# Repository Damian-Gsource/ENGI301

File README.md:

# ENGI301: Drone project
Repository for ENGI301 course work
The first project that was worked on for this course was a DIY drone/quadcopter fitted with a camera.
This drone would be able to fly remotely and have a camera attached to it as well. It is worth noting that the drone is a continuous work in progress. 

Needed Installations

(Pocketbeagle)

sudo apt-get update

sudo apt-get install build-essential python-dev python-setuptools python-smbus -y

sudo apt-get install python-pip python3-pip -y

sudo apt-get install zip

sudo pip3 install --upgrade setuptools

sudo pip3 install --upgrade Adafruit_BBIO

sudo pip3 install adafruit-blinka

sudo apt-get install python3-opencv

Needed Installations
https://www.solidworks.com/

Hackster.io link
https://www.hackster.io/team-diy-drone/diy-quadcopter-for-all-your-droning-needs-14d5b1

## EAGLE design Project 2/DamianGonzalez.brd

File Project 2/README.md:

The MIT License (MIT)

Copyright (c) 2022Damian Gonzalez

Permission is hereby granted, free of charge, to any person obtaining a copy of this software and associated documentation files (the "Software"), to deal in the Software without restriction, including without limitation the rights to use, copy, modify, merge, publish, distribute, sublicense, and/or sell copies of the Software, and to permit persons to whom the Software is furnished to do so, subject to the following conditions:

The above copyright notice and this permission notice shall be included in all copies or substantial portions of the Software.

THE SOFTWARE IS PROVIDED "AS IS", WITHOUT WARRANTY OF ANY KIND, EXPRESS OR IMPLIED, INCLUDING BUT NOT LIMITED TO THE WARRANTIES OF MERCHANTABILITY, FITNESS FOR A PARTICULAR PURPOSE AND NONINFRINGEMENT. IN NO EVENT SHALL THE AUTHORS OR COPYRIGHT HOLDERS BE LIABLE FOR ANY CLAIM, DAMAGES OR OTHER LIABILITY, WHETHER IN AN ACTION OF CONTRACT, TORT OR OTHERWISE, ARISING FROM, OUT OF OR IN CONNECTION WITH THE SOFTWARE OR THE USE OR OTHER DEALINGS IN THE SOFTWARE.

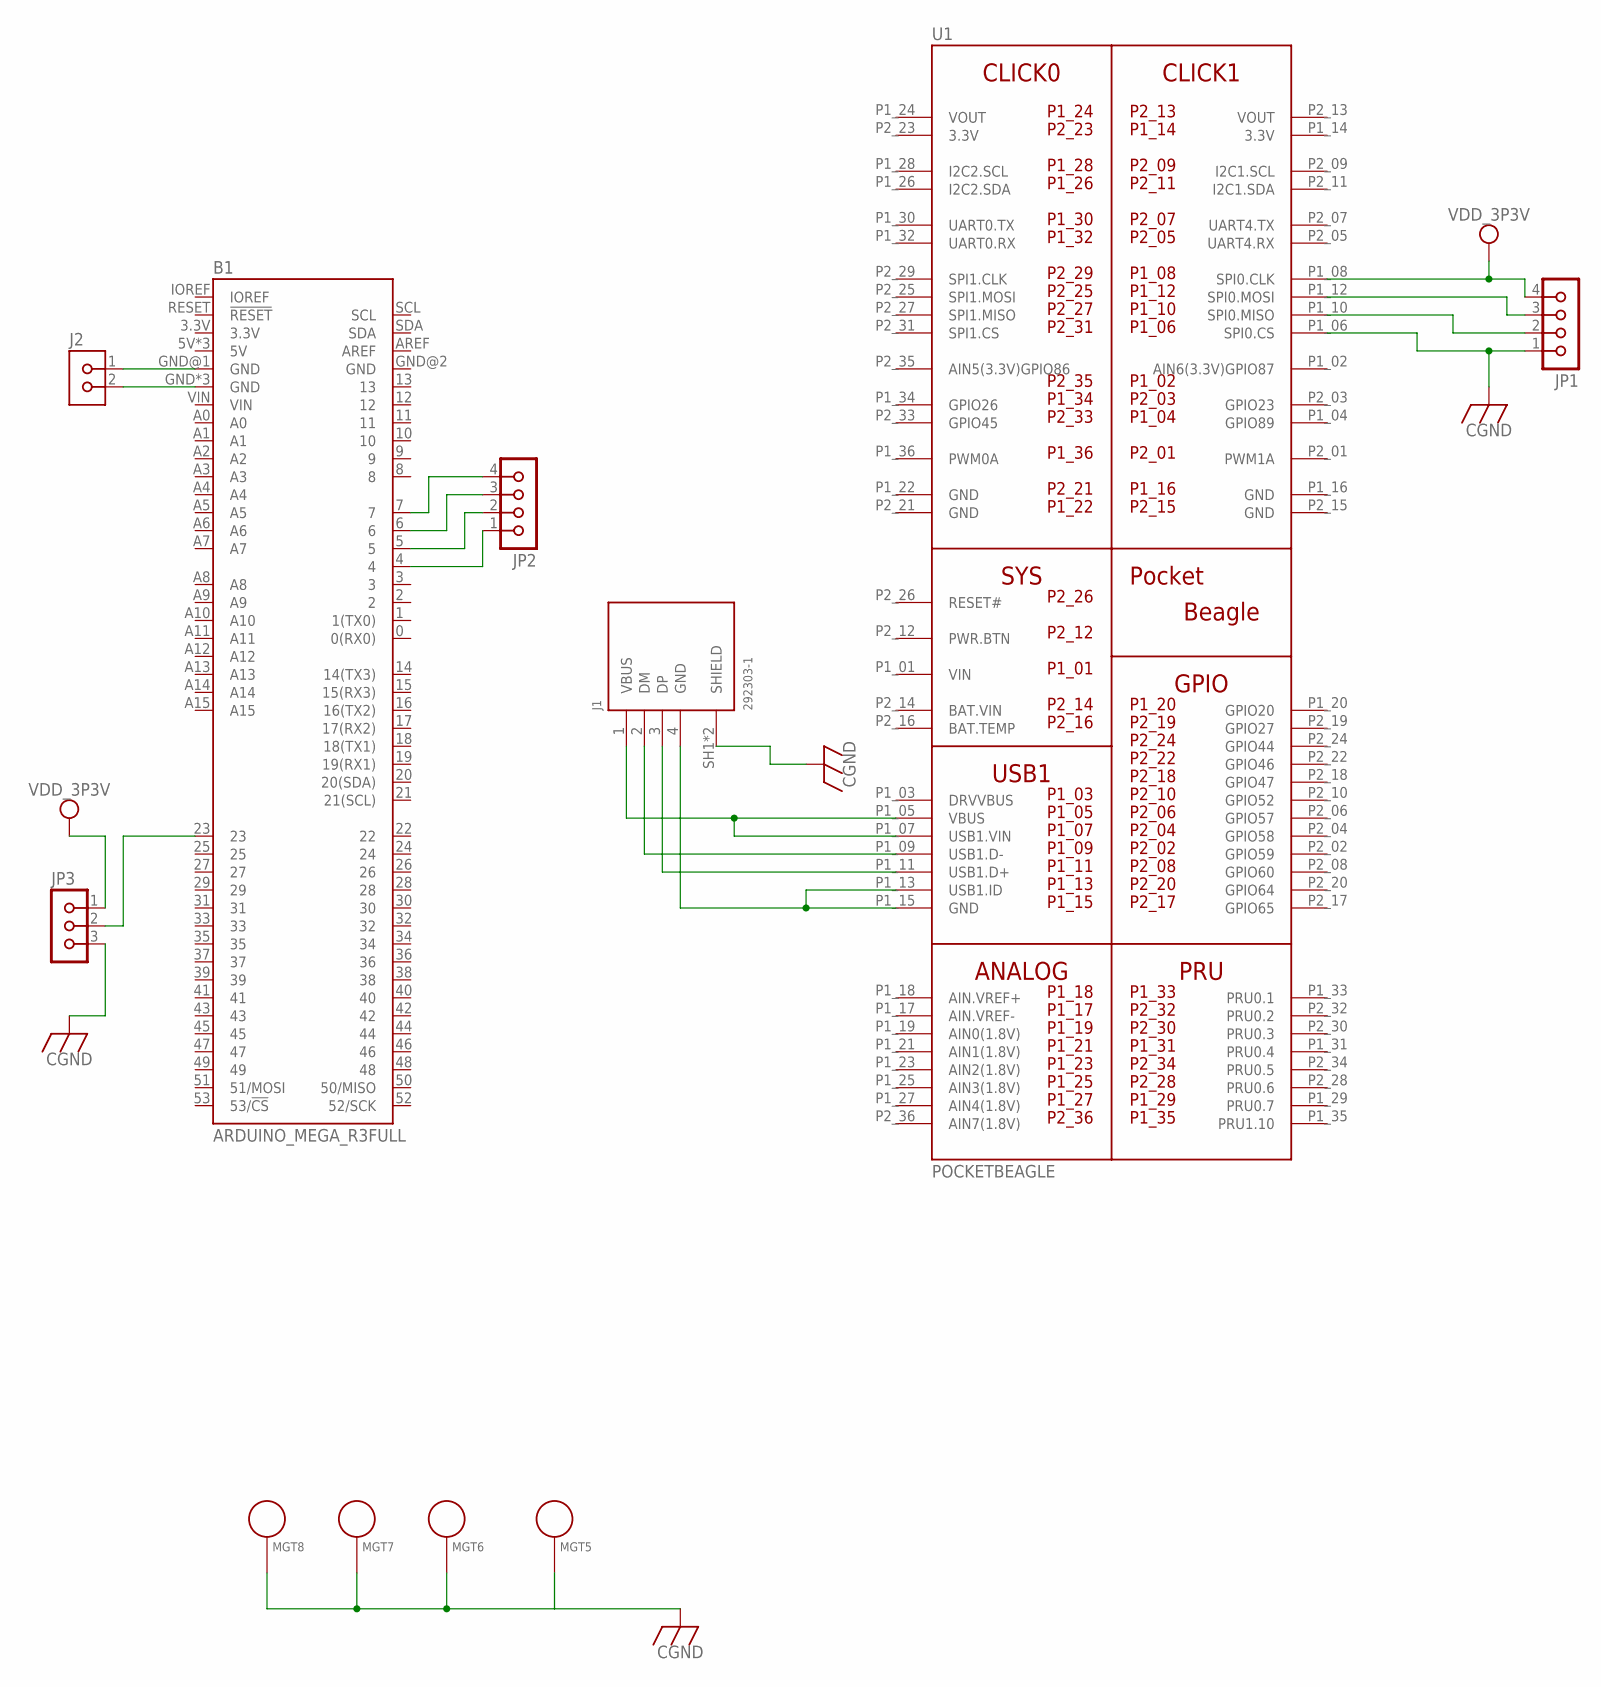
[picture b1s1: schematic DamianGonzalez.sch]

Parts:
B1: ARDUINO_MEGA_R3FULL; ARDUINO_MEGA_NO_SILK
J1: 292303-1; TE_292303-1
J2: PINHD-1X2; H1X2-2.54
JP1, JP2: PINHD-1X4; H1X4-2.54
JP3: PINHD-1X3; H1X3-2.54
MGT5, MGT6, MGT7, MGT8: MOUNTING_HOLE
U1: POCKETBEAGLE

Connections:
3.3V: U1.P1_14 (3.3V), U1.P2_23 (3.3V)
BAT.VIN: U1.P2_14 (BAT.VIN)
CGND: J1.SH1 (SHIELD), J1.SH2 (SHIELD), JP1.1, JP3.3, MGT5.P$1, MGT6.P$1, MGT7.P$1, MGT8.P$1, U1.P1_06 (SPI0.CS)
GND: U1.P1_16 (GND), U1.P1_22 (GND), U1.P2_15 (GND), U1.P2_21 (GND)
unnamed: J1.1 (VBUS), U1.P1_05 (VBUS), U1.P1_07 (USB1.VIN)
unnamed: J1.4 (GND), U1.P1_13 (USB1.ID), U1.P1_15 (GND)
unnamed: J1.3 (DP), U1.P1_11 (USB1.D+)
unnamed: J1.2 (DM), U1.P1_09 (USB1.D-)
unnamed: JP1.3, U1.P1_12 (SPI0.MOSI)
unnamed: JP1.2, U1.P1_10 (SPI0.MISO)
unnamed: B1.7, JP2.4
unnamed: B1.6, JP2.3
unnamed: B1.5, JP2.2
unnamed: B1.4, JP2.1
unnamed: B1.GND@1 (GND), J2.1
unnamed: B1.GND, B1.GND@3 (GND), B1.GND@4 (GND), J2.2
unnamed: B1.23, JP3.2
VDD_3P3V: JP1.4, JP3.1, U1.P1_08 (SPI0.CLK)
VIN: U1.P1_01 (VIN)
VOUT: U1.P1_24 (VOUT), U1.P2_13 (VOUT)

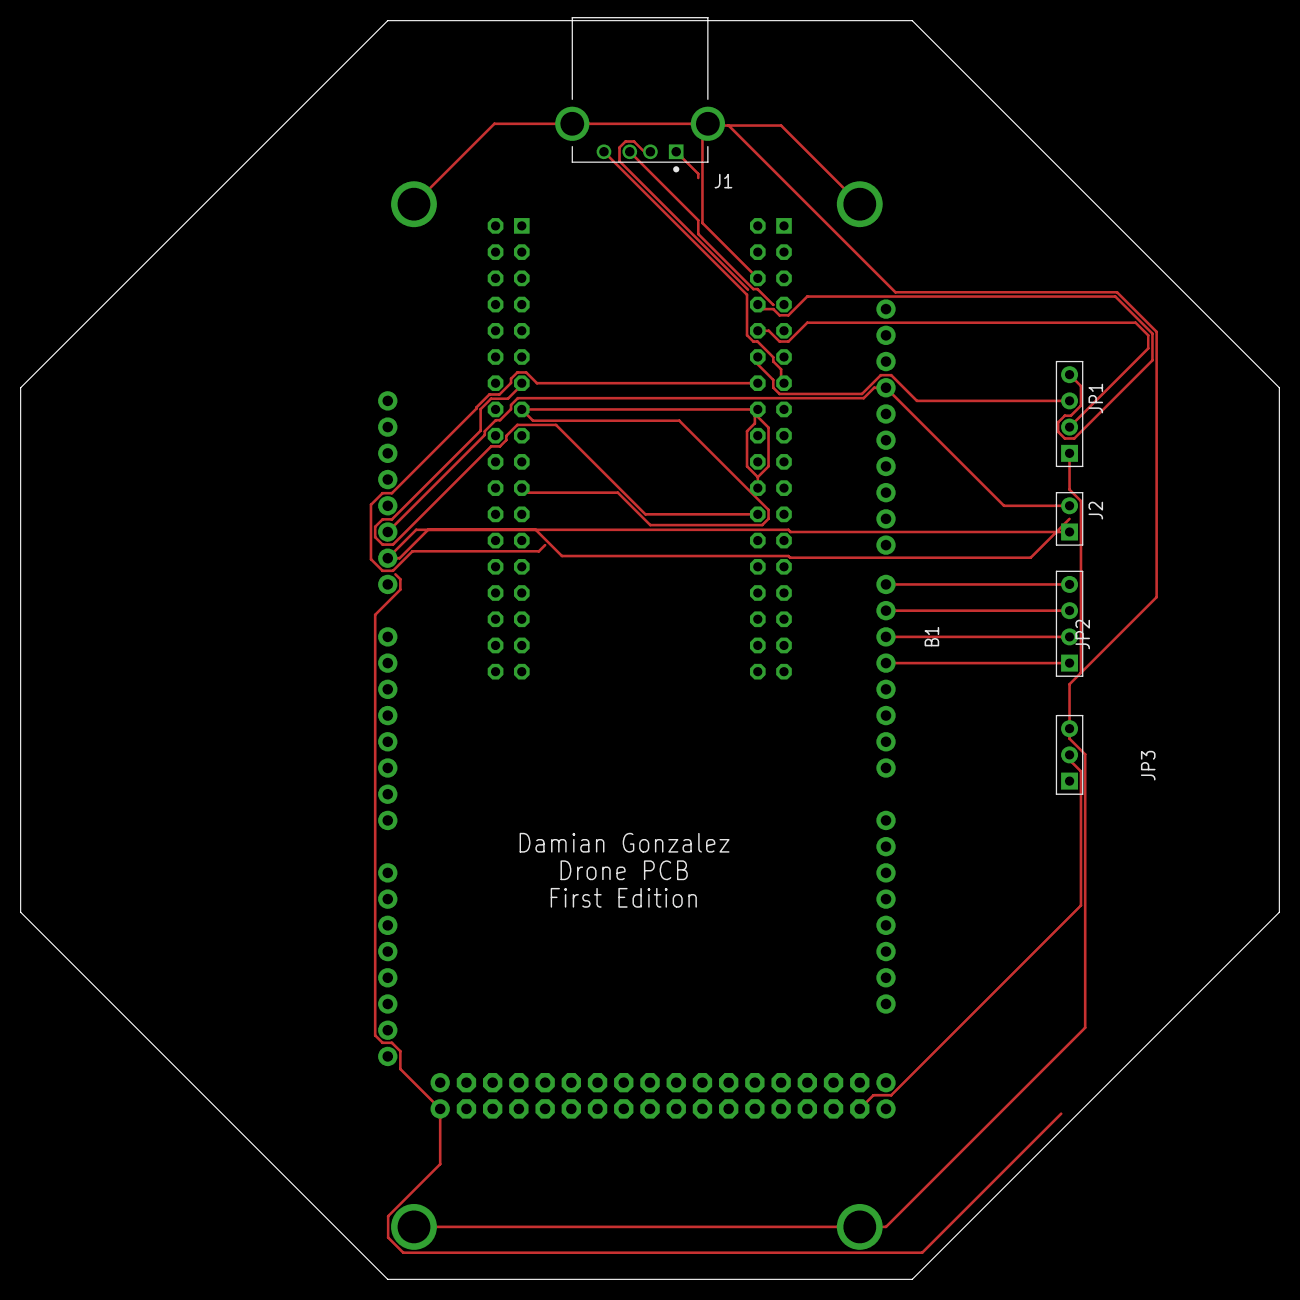
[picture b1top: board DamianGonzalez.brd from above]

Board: 2 copper layers, 121.9 x 121.9 mm, 11 parts (1 on the bottom side), 18 nets.

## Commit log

2022-02-01 Updating README.md
    We left the ENGI301 heading as is, and we added the second line "Repository for ENGI301 course work".
2022-02-15 Create simple_calc
    This is the simple calculator that we created in class.
2022-02-16 Update simple_calc
2022-04-04 Create Camera.py
    This is the file for adding in the camera through the pocketbeagle
2022-04-05 Create Camera_V2.py
    New and improved version of the camera code
2022-04-05 Add files via upload
    3D stl files that can be used to print them out
2022-04-05 Create LICENSE
2022-05-04 project 2
2022-05-04 Board Straight from Eagle
2022-05-04 Drone Schematic
2022-05-04 Schematic PDF Drone
2022-05-04 Libraries for Eagle
2022-05-04 BOM for Drone PCB
2022-05-04 Library filled with parts I created
